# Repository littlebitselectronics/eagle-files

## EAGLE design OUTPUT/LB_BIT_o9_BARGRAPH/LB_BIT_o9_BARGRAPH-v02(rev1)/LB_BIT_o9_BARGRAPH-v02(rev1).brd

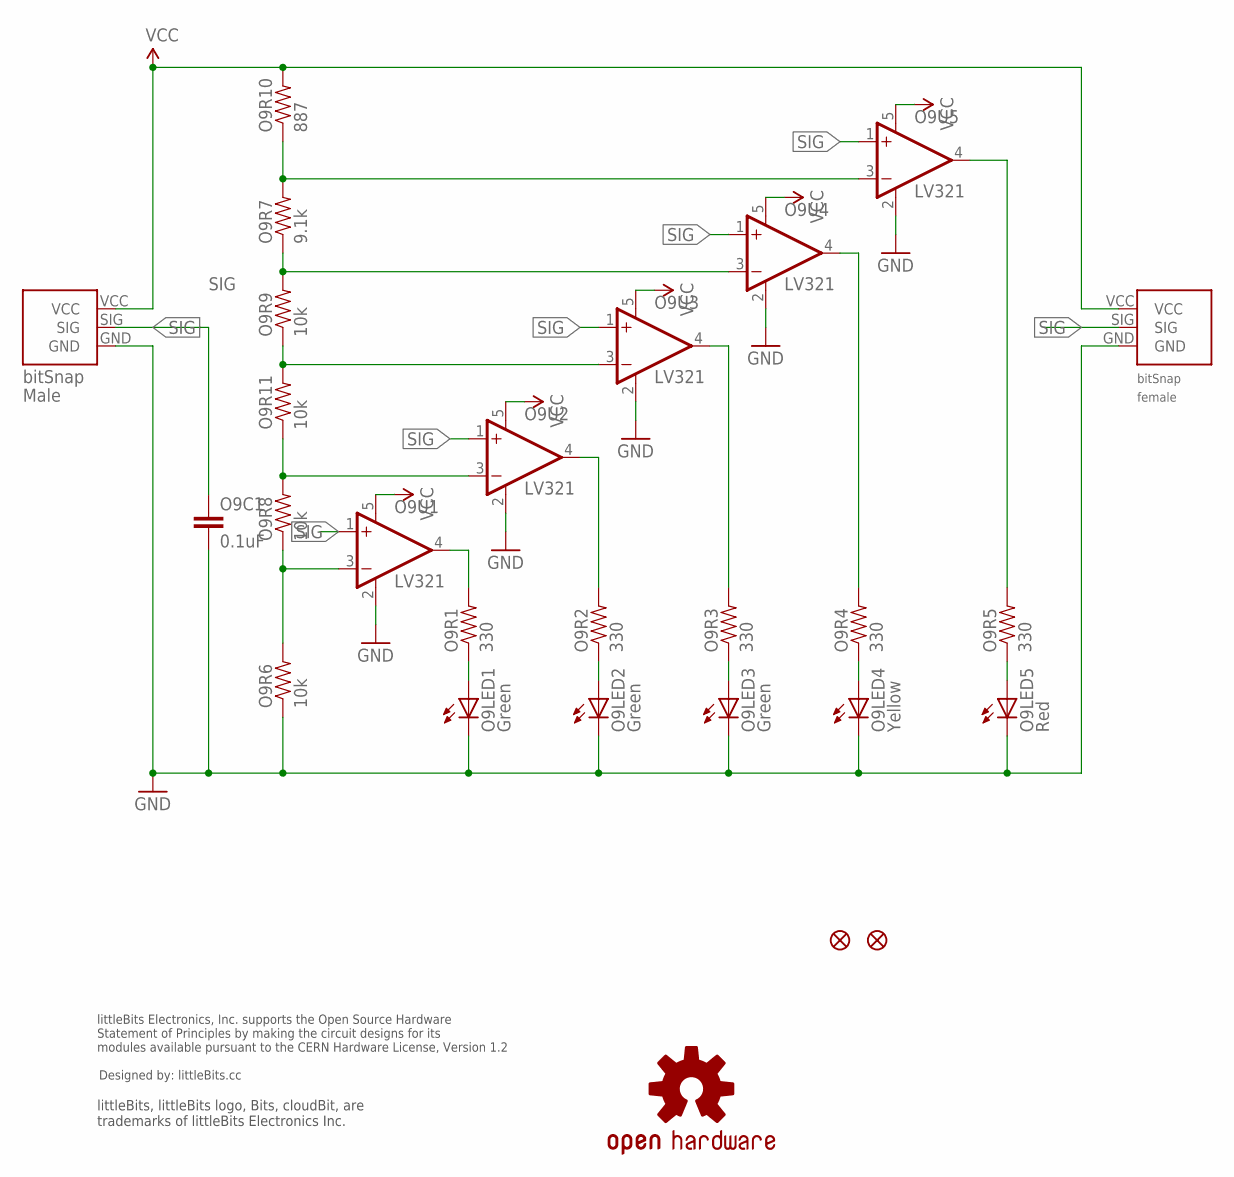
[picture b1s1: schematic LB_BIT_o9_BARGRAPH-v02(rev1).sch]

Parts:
JP1, JP2: FIDUCIAL1X2.5; FIDUCIAL-1X2.5
O9BSF: BITSNAP_FEMALE
O9BSM: BITSNAP_MALE
O9C1: 0.1uF; 0603-CAP
O9LED1, O9LED2, O9LED3: Green; LED-1206
O9LED4: Yellow; LED-1206
O9LED5: Red; LED-1206
O9R1, O9R2, O9R3, O9R4, O9R5: 330; 0603-RES
O9R6, O9R8, O9R9, O9R11: 10k; 0603-RES
O9R7: 9.1k; 0603-RES
O9R10: 887; 0603-RES
O9U1, O9U2, O9U3, O9U4, O9U5: LV321; SC70-5
U$1: OSHWCREDIT
U$3: OSHW-LOGOL; OSHW-LOGO-L

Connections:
GND: O9BSF.GND, O9BSM.GND, O9C1.2, O9LED1.C, O9LED2.C, O9LED3.C, O9LED4.C, O9LED5.C, O9R6.1, O9U1.2 (V-), O9U2.2 (V-), O9U3.2 (V-), O9U4.2 (V-), O9U5.2 (V-)
unnamed: O9R1.2, O9U1.4 (OUT)
unnamed: O9LED1.A, O9R1.1
unnamed: O9LED2.A, O9R2.1
unnamed: O9LED3.A, O9R3.1
unnamed: O9LED4.A, O9R4.1
unnamed: O9LED5.A, O9R5.1
unnamed: O9R2.2, O9U2.4 (OUT)
unnamed: O9R3.2, O9U3.4 (OUT)
unnamed: O9R4.2, O9U4.4 (OUT)
unnamed: O9R5.2, O9U5.4 (OUT)
unnamed: O9R6.2, O9R8.1, O9U1.3 (-IN)
unnamed: O9R8.2, O9R11.1, O9U2.3 (-IN)
unnamed: O9R9.1, O9R11.2, O9U3.3 (-IN)
unnamed: O9R7.1, O9R9.2, O9U4.3 (-IN)
unnamed: O9R7.2, O9R10.1, O9U5.3 (-IN)
SIG: O9BSF.SIG, O9BSM.SIG, O9C1.1, O9U1.1 (+IN), O9U2.1 (+IN), O9U3.1 (+IN), O9U4.1 (+IN), O9U5.1 (+IN)
VCC: O9BSF.VCC, O9BSM.VCC, O9R10.2, O9U1.5 (V+), O9U2.5 (V+), O9U3.5 (V+), O9U4.5 (V+), O9U5.5 (V+)

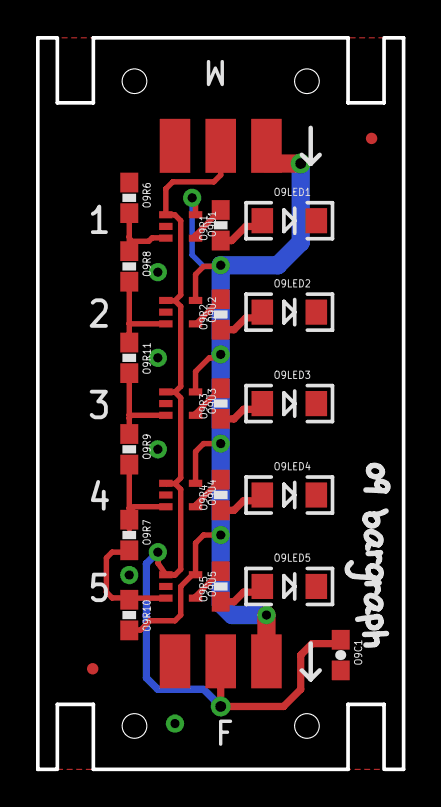
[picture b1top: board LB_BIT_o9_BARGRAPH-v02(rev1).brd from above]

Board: 2 copper layers, 20.3 x 40.6 mm, 29 parts (0 on the bottom side), 18 nets.

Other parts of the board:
U$10: OSHW_FILLX150_NOTEXT

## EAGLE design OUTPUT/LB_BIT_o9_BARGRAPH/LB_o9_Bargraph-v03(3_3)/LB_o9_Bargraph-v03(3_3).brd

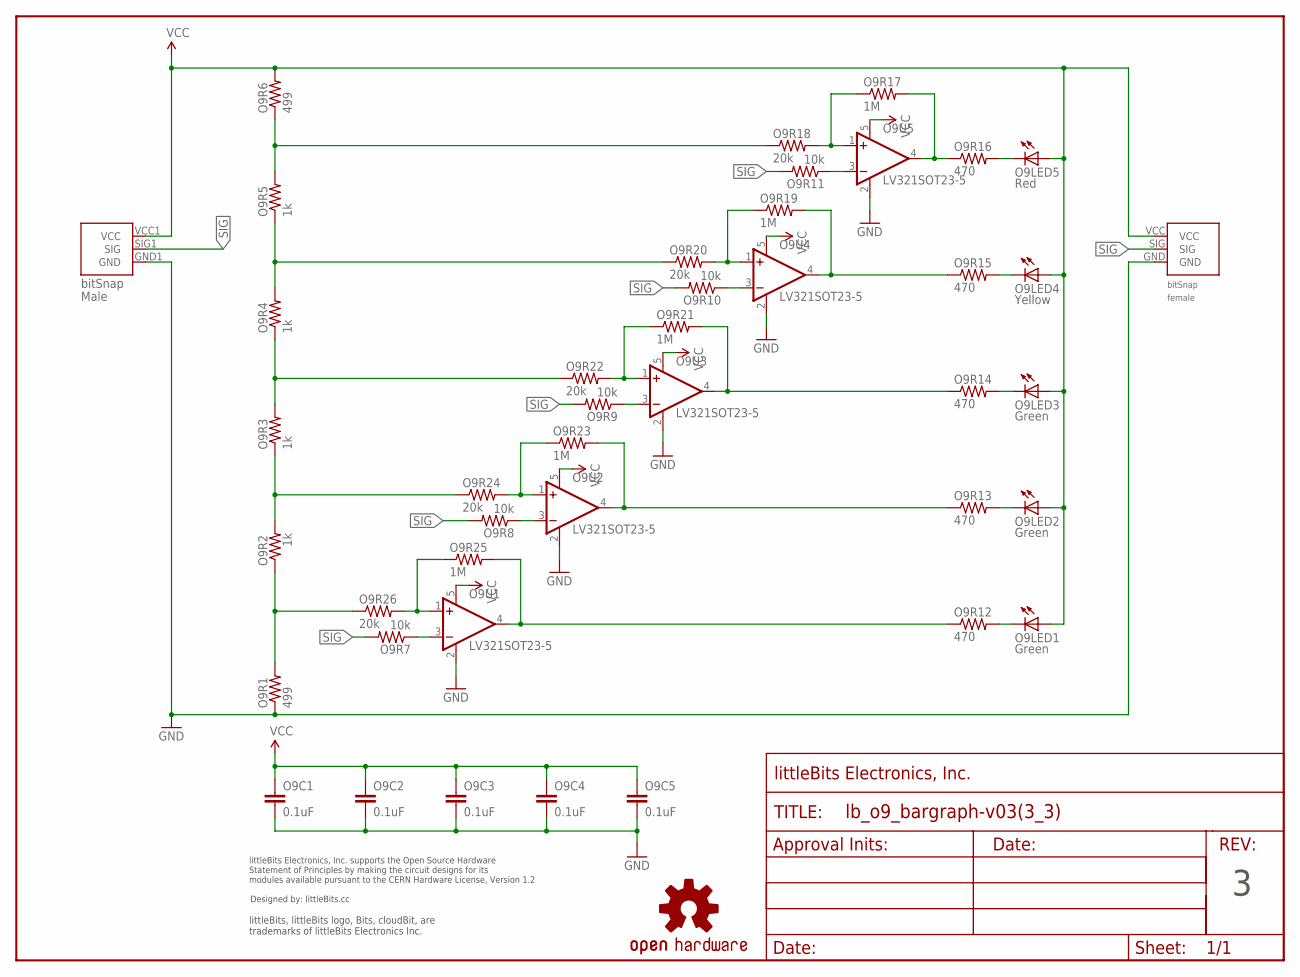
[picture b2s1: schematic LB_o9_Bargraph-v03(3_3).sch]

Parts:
09BSF1: BITSNAP_V03_FEMALE
O9BSM1: BITSNAP_V03_MALE
O9C1, O9C2, O9C3, O9C4, O9C5: 0.1uF; 0603-CAP
O9LED1, O9LED2, O9LED3: Green; LED-1206
O9LED4: Yellow; LED-1206
O9LED5: Red; LED-1206
O9R1, O9R6: 499; 0603-RES
O9R2, O9R3, O9R4, O9R5: 1k; 0603-RES
O9R7, O9R8, O9R9, O9R10, O9R11: 10k; 0603-RES
O9R12, O9R13, O9R14, O9R15, O9R16: 470; 0603-RES
O9R17, O9R19, O9R21, O9R23, O9R25: 1M; 0603-RES
O9R18, O9R20, O9R22, O9R24, O9R26: 20k; 0603-RES
O9U1, O9U2, O9U3, O9U4, O9U5: LV321SOT23-5; SOT23-5
U$1: OSHWCREDIT
U$2: FRAME-LETTER-OHWOHW; FABDWG01-OHW
U$4: OSHW-LOGOL; OSHW-LOGO-L

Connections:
GND: 09BSF1.GND, O9BSM1.GND1 (GND), O9C1.2, O9C2.2, O9C3.2, O9C4.2, O9C5.2, O9R1.1, O9U1.2 (V-), O9U2.2 (V-), O9U3.2 (V-), O9U4.2 (V-), O9U5.2 (V-)
unnamed: O9R7.1, O9U1.3 (-IN)
unnamed: O9LED1.C, O9R12.2
unnamed: O9LED2.C, O9R13.2
unnamed: O9LED3.C, O9R14.2
unnamed: O9LED4.C, O9R15.2
unnamed: O9R16.1, O9R17.2, O9U5.4 (OUT)
unnamed: O9R11.1, O9U5.3 (-IN)
unnamed: O9LED5.C, O9R16.2
unnamed: O9R17.1, O9R18.2, O9U5.1 (+IN)
unnamed: O9R15.1, O9R19.2, O9U4.4 (OUT)
unnamed: O9R10.1, O9U4.3 (-IN)
unnamed: O9R19.1, O9R20.2, O9U4.1 (+IN)
unnamed: O9R21.1, O9R22.2, O9U3.1 (+IN)
unnamed: O9R1.2, O9R2.1, O9R26.1
unnamed: O9R2.2, O9R3.1, O9R24.1
unnamed: O9R3.2, O9R4.1, O9R22.1
unnamed: O9R4.2, O9R5.1, O9R20.1
unnamed: O9R9.1, O9U3.3 (-IN)
unnamed: O9R14.1, O9R21.2, O9U3.4 (OUT)
unnamed: O9R5.2, O9R6.1, O9R18.1
unnamed: O9R8.1, O9U2.3 (-IN)
unnamed: O9R23.1, O9R24.2, O9U2.1 (+IN)
unnamed: O9R13.1, O9R23.2, O9U2.4 (OUT)
unnamed: O9R12.1, O9R25.2, O9U1.4 (OUT)
unnamed: O9R25.1, O9R26.2, O9U1.1 (+IN)
SIG: 09BSF1.SIG, O9BSM1.SIG1 (SIG), O9R7.2, O9R8.2, O9R9.2, O9R10.2, O9R11.2
VCC: 09BSF1.VCC, O9BSM1.VCC1 (VCC), O9C1.1, O9C2.1, O9C3.1, O9C4.1, O9C5.1, O9LED1.A, O9LED2.A, O9LED3.A, O9LED4.A, O9LED5.A, O9R6.2, O9U1.5 (V+), O9U2.5 (V+), O9U3.5 (V+), O9U4.5 (V+), O9U5.5 (V+)

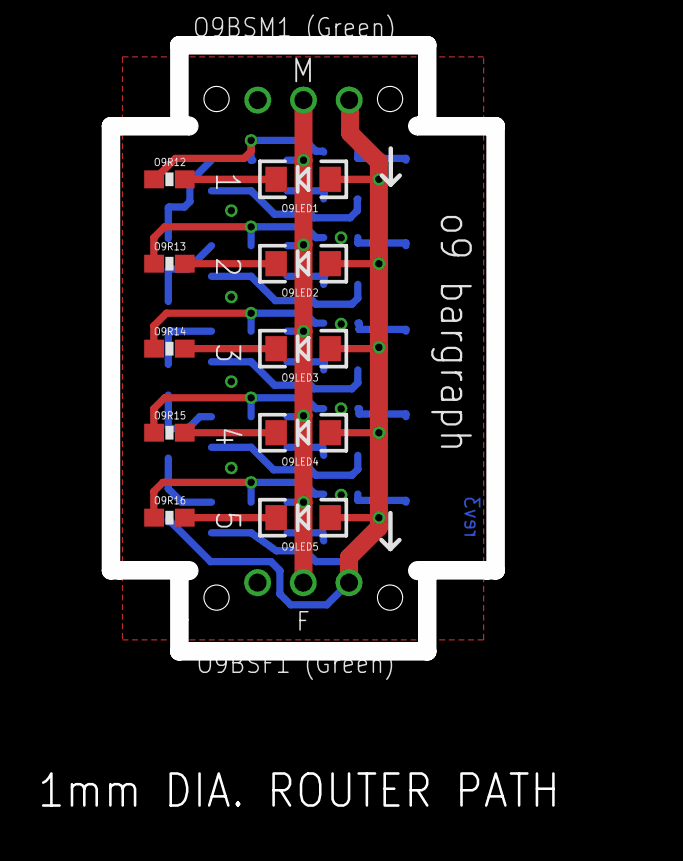
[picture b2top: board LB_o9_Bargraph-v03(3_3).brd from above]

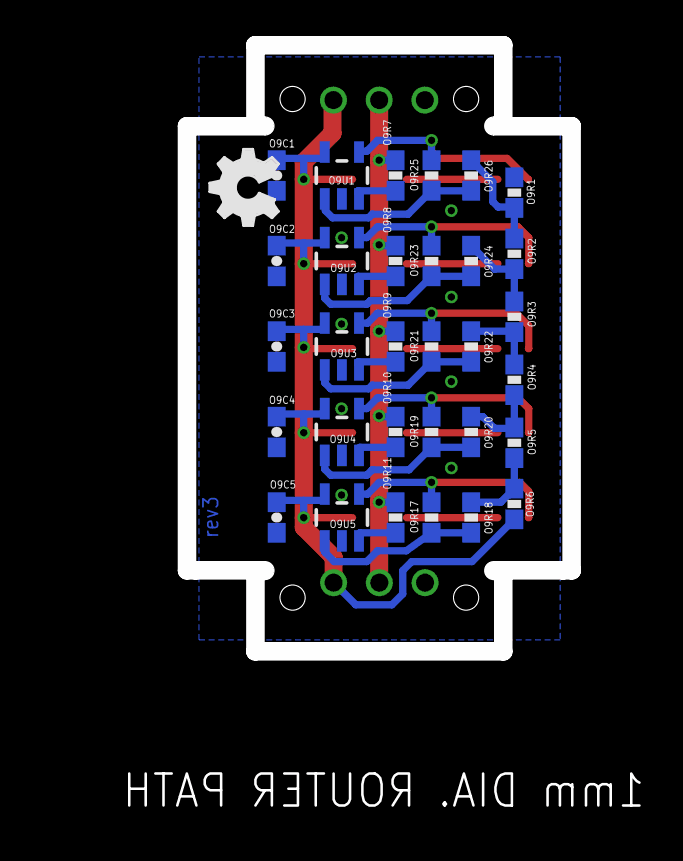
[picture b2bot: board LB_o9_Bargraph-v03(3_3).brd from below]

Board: 2 copper layers, 21.4 x 33.7 mm, 47 parts (31 on the bottom side), 28 nets.

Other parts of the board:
U$10: OSHW_FILLX150_NOTEXT

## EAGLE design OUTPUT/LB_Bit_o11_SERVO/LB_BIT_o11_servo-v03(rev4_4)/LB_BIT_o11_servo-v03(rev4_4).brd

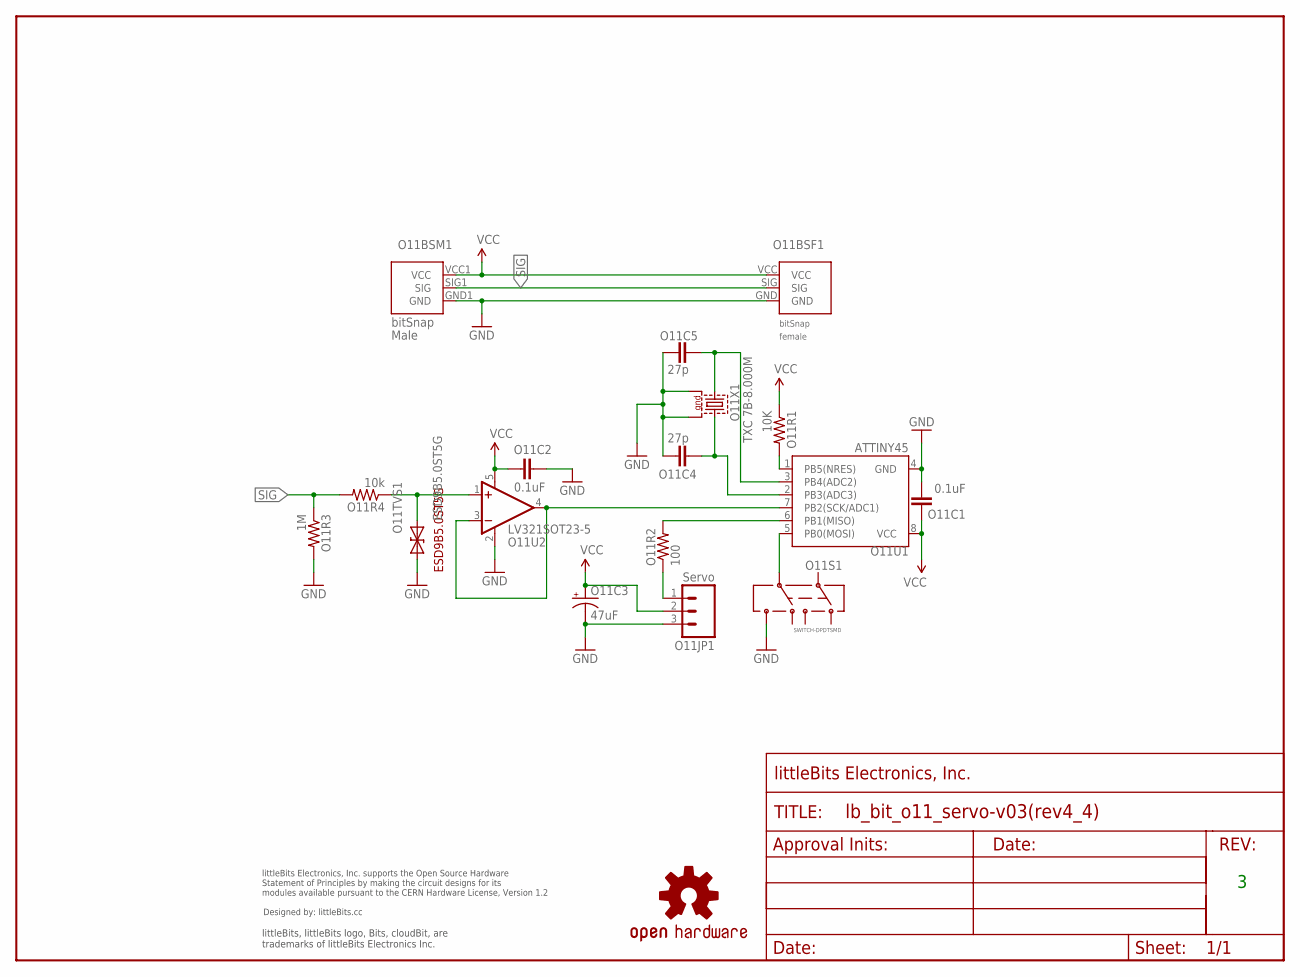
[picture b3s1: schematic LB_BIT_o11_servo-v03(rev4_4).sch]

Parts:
O11BSF1: BITSNAP_V03_FEMALE
O11BSM1: BITSNAP_V03_MALE
O11C1, O11C2: 0.1uF; 0603-CAP
O11C3: 47uF; EIA3216
O11C4, O11C5: 27p; 0603-CAP
O11JP1: Servo; 1X03
O11R1: 10K; 0603-RES
O11R2: 100; 0603-RES
O11R3: 1M; 0603-RES
O11R4: 10k; 0603-RES
O11S1: SWITCH-DPDTSMD; AYZ0202
O11TVS1: ESD9B5.0ST5G; SOD-923
O11U1: ATTINY45; SO08-EIAJ
O11U2: LV321SOT23-5; SOT23-5
O11X1: TXC 7B-8.000M; CRYSTAL-SMD-7B-SERIES-5X3.2MM
U$1: FRAME-LETTER-OHWOHW; FABDWG01-OHW
U$13: OSHWCREDIT
U$25: OSHW-LOGOL; OSHW-LOGO-L

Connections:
GND: O11BSF1.GND, O11BSM1.GND1 (GND), O11C1.2, O11C2.2, O11C3.-, O11C4.1, O11C5.2, O11JP1.3, O11R3.2, O11S1.6, O11TVS1.1 (A), O11U1.4 (GND), O11U2.2 (V-), O11X1.P$2 (2), O11X1.P$4 (4)
unnamed: O11C5.1, O11U1.3 (PB4(ADC2)), O11X1.P$1 (1)
unnamed: O11C4.2, O11U1.2 (PB3(ADC3)), O11X1.P$3 (3)
unnamed: O11R1.2, O11U1.1 (PB5(NRES))
unnamed: O11S1.5, O11U1.5 (PB0(MOSI))
unnamed: O11JP1.1, O11R2.1
unnamed: O11R2.2, O11U1.6 (PB1(MISO))
unnamed: O11U1.7 (PB2(SCK/ADC1)), O11U2.3 (-IN), O11U2.4 (OUT)
unnamed: O11R4.1, O11TVS1.2 (C), O11U2.1 (+IN)
SIG: O11BSF1.SIG, O11BSM1.SIG1 (SIG), O11R3.1, O11R4.2
VCC: O11BSF1.VCC, O11BSM1.VCC1 (VCC), O11C1.1, O11C2.1, O11C3.+, O11JP1.2, O11R1.1, O11U1.8 (VCC), O11U2.5 (V+)

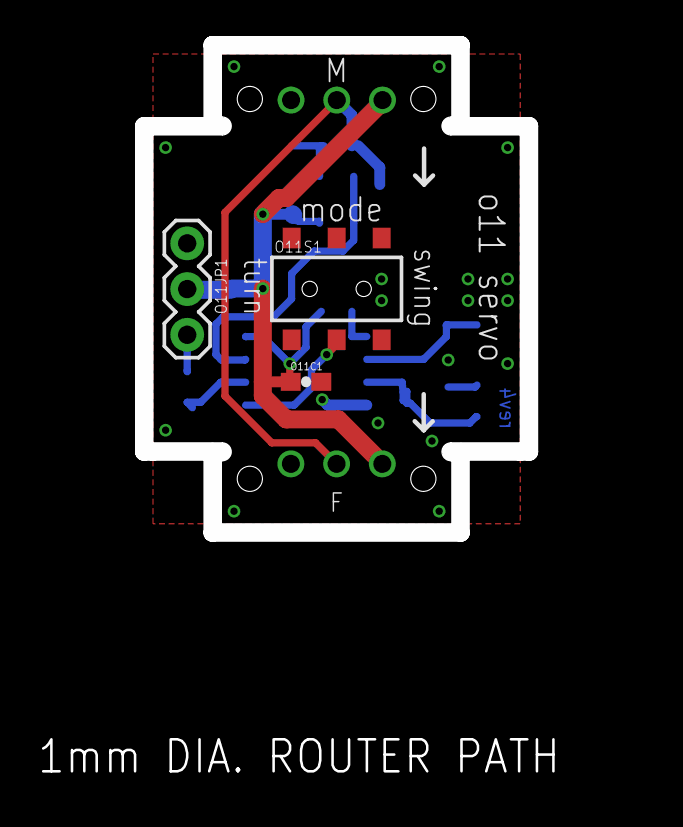
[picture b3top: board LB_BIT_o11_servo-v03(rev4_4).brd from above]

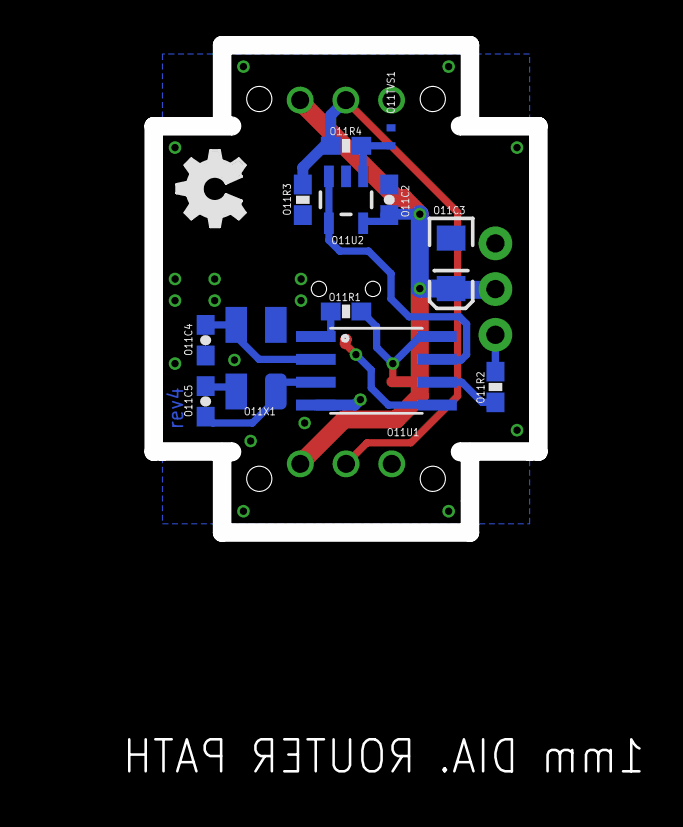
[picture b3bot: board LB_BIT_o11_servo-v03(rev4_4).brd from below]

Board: 2 copper layers, 21.4 x 27.1 mm, 21 parts (12 on the bottom side), 11 nets.

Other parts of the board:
U$26: OSHW_FILLX150_NOTEXT

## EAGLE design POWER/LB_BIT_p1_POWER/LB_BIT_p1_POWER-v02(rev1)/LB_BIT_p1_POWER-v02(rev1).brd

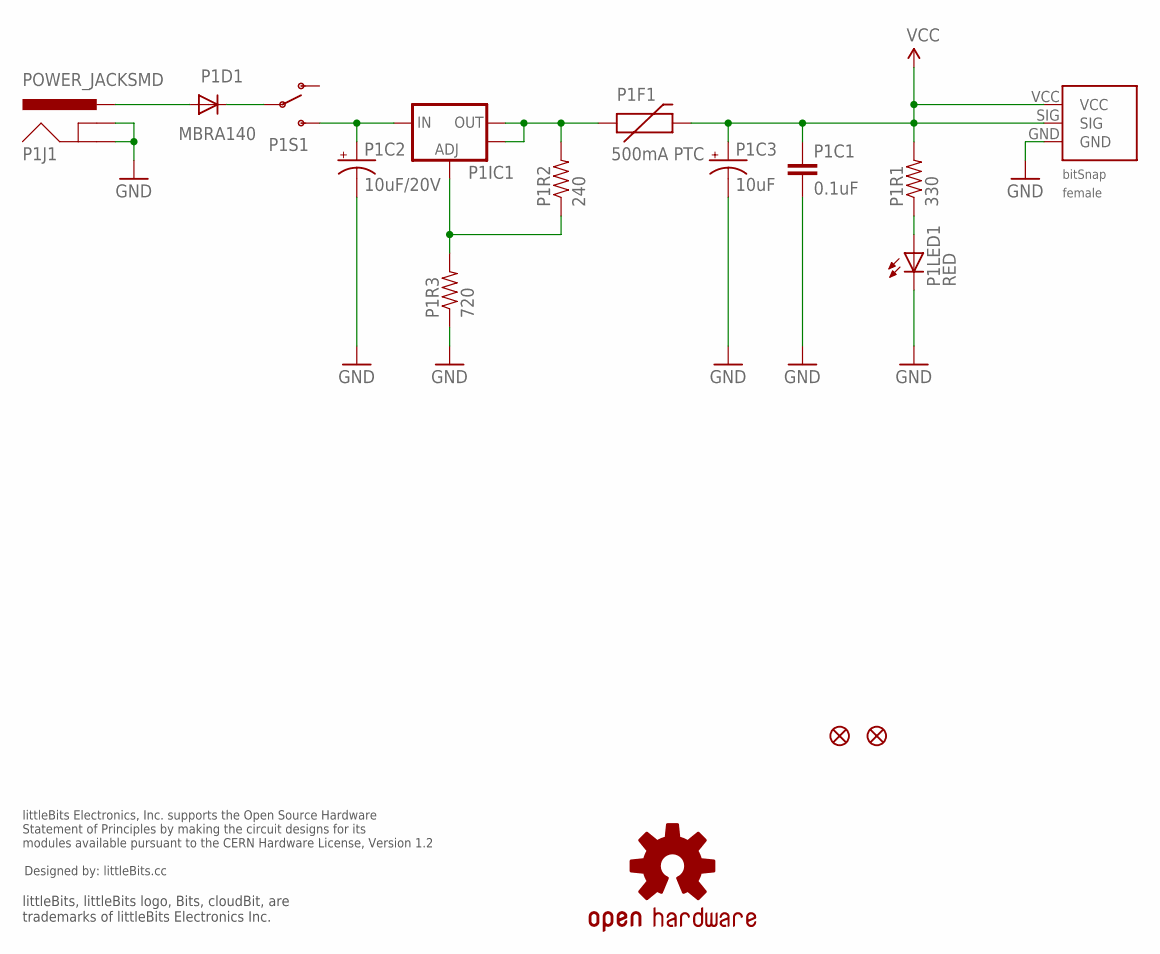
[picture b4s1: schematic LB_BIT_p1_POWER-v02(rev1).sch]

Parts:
JP1, JP2: FIDUCIAL1X2.5; FIDUCIAL-1X2.5
P1BSF: BITSNAP_FEMALE
P1C1: 0.1uF; 0603-CAP
P1C2: 10uF/20V; EIA3528
P1C3: 10uF; EIA3216
P1D1: MBRA140; SMA-DIODE
P1F1: 500mA PTC; PTC-1206
P1IC1: V_REG_LM1117SOT223; SOT223
P1J1: POWER_JACKSMD; POWER_JACK_SMD
P1LED1: RED; LED-1206
P1R1: 330; 0603-RES
P1R2: 240; 0603-RES
P1R3: 720; 0603-RES
P1S1: SWITCH-SPSTSMD; AYZ0202
U$1: OSHWCREDIT
U$3: OSHW-LOGOL; OSHW-LOGO-L

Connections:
GND: P1BSF.GND, P1C1.2, P1C2.C (-), P1C3.C (-), P1J1.GND (GNDBREAK), P1J1.P$4 (GND), P1LED1.C, P1R3.1
unnamed: P1D1.C, P1S1.2
unnamed: P1F1.1, P1IC1.2 (OUT), P1IC1.4 (OUT), P1R2.2
unnamed: P1IC1.1 (ADJ), P1R2.1, P1R3.2
unnamed: P1C2.A (+), P1IC1.3 (IN), P1S1.3 (S)
unnamed: P1D1.A, P1J1.VIN0 (PWR)
unnamed: P1LED1.A, P1R1.1
VCC: P1BSF.SIG, P1BSF.VCC, P1C1.1, P1C3.A (+), P1F1.2, P1R1.2

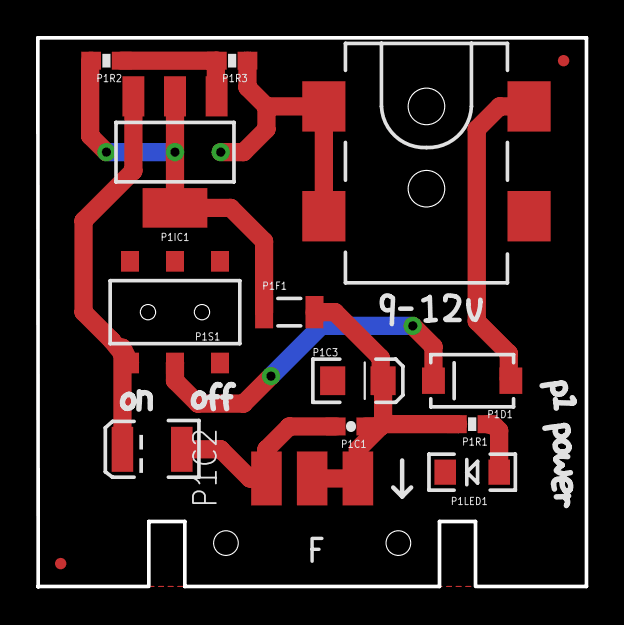
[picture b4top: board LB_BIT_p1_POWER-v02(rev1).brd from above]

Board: 2 copper layers, 30.5 x 30.5 mm, 18 parts (0 on the bottom side), 8 nets.

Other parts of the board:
U$2: OSHW_FILLX150_NOTEXT

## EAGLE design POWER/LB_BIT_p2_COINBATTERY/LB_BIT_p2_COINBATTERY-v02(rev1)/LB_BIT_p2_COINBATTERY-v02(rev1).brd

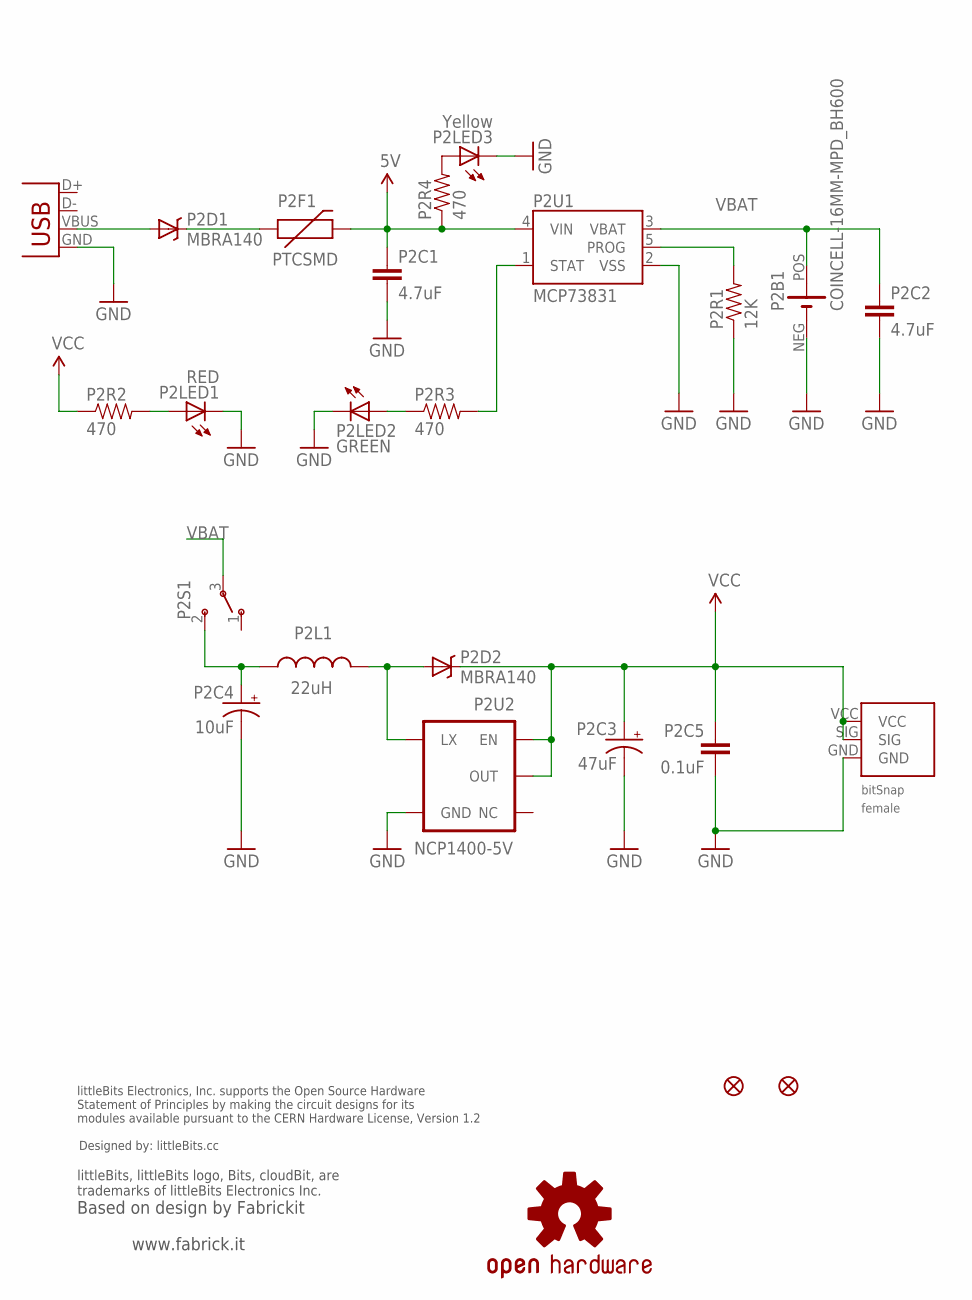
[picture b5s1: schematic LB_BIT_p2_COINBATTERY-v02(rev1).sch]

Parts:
JP1, JP2: FIDUCIAL1X2; FIDUCIAL-1X2
P2B1: COINCELL-16MM-MPD_BH600
P2BSF: BITSNAP_FEMALE
P2C1, P2C2: 4.7uF; 0603-CAP
P2C3: 47uF; EIA3528
P2C4: 10uF; EIA3216
P2C5: 0.1uF; 0603-CAP
P2D1, P2D2: MBRA140; SMA-DIODE
P2F1: PTCSMD; PTC-1206
P2L1: 22uH; INDUCTOR-TAITO_YUDEN_NR6028T220M
P2LED1: RED; LED-1206
P2LED2: GREEN; LED-1206
P2LED3: Yellow; LED-1206
P2R1: 12K; 0603-RES
P2R2, P2R3, P2R4: 470; 0603-RES
P2S1: SWITCH-SMD-SLIDE-CSS1210TB; COPAL_CSS1210TB
P2U1: MCP73831; SOT23-5
P2U2: NCP1400-5V; SOT23-5
P2X1: USB-MICROB
U$3: OSHWCREDIT
U$4: OSHW-LOGOL; OSHW-LOGO-L

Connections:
5V: P2C1.1, P2F1.2, P2R4.1, P2U1.4 (VIN)
GND: P2B1.NEG (-), P2BSF.GND, P2C1.2, P2C2.2, P2C3.C (-), P2C4.C (-), P2C5.2, P2LED1.C, P2LED2.C, P2LED3.C, P2R1.1, P2U1.2 (VSS), P2U2.4 (GND), P2X1.GND
unnamed: P2D1.A, P2X1.VBUS
unnamed: P2D1.C, P2F1.1
unnamed: P2LED3.A, P2R4.2
unnamed: P2LED1.A, P2R2.2
unnamed: P2LED2.A, P2R3.1
unnamed: P2D2.A, P2L1.P$1 (1), P2U2.5 (LX)
PROG: P2R1.2, P2U1.5 (PROG)
RAW: P2C4.A (+), P2L1.P$2 (2), P2S1.2
STAT: P2R3.2, P2U1.1 (STAT)
VBAT: P2B1.POS (+), P2C2.1, P2S1.3, P2U1.3 (VBAT)
VCC: P2BSF.SIG, P2BSF.VCC, P2C3.A (+), P2C5.1, P2D2.C, P2R2.1, P2U2.1 (EN), P2U2.2 (OUT)

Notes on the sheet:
Based on design by Fabrickit
www.fabrick.it

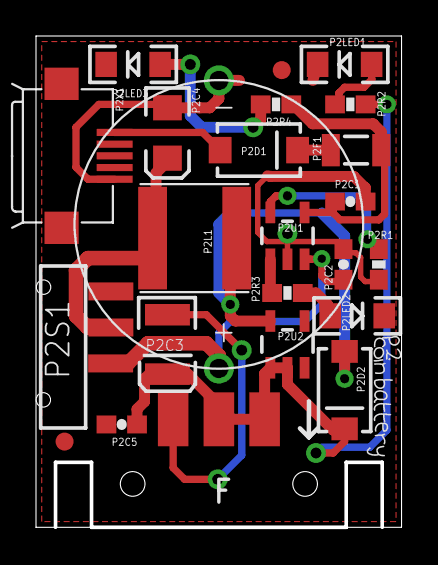
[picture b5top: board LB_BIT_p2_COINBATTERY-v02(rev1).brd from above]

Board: 2 copper layers, 20.3 x 27.3 mm, 40 parts (0 on the bottom side), 13 nets.

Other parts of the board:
E$1: O_SMALL
E$2: I_SMALL
E$3: N_SMALL
E$4: B_SMALL
E$5: A_BATTERY
E$6, E$7: T_SMALL
E$8: E_SMALL
E$9: R_SMALL
E$10: Y_SMALL
E$11: P_SMALL
E$12: 2_SMALL
U$1: C_SMALL
U$7: OSHW_FILLX150_NOTEXT

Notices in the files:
parts and their libraries:
LITTLEBITS: Released under the Creative Commons Attribution Share-Alike 3.0 License
LITTLEBITS: http://creativecommons.org/license/by-sa/3.0
LITTLEBITS: http://creativecommons.org/licenses/by-sa/3.0
LITTLEBITS: modules available pursuant to the CERN Hardware License,
Version 1.2
